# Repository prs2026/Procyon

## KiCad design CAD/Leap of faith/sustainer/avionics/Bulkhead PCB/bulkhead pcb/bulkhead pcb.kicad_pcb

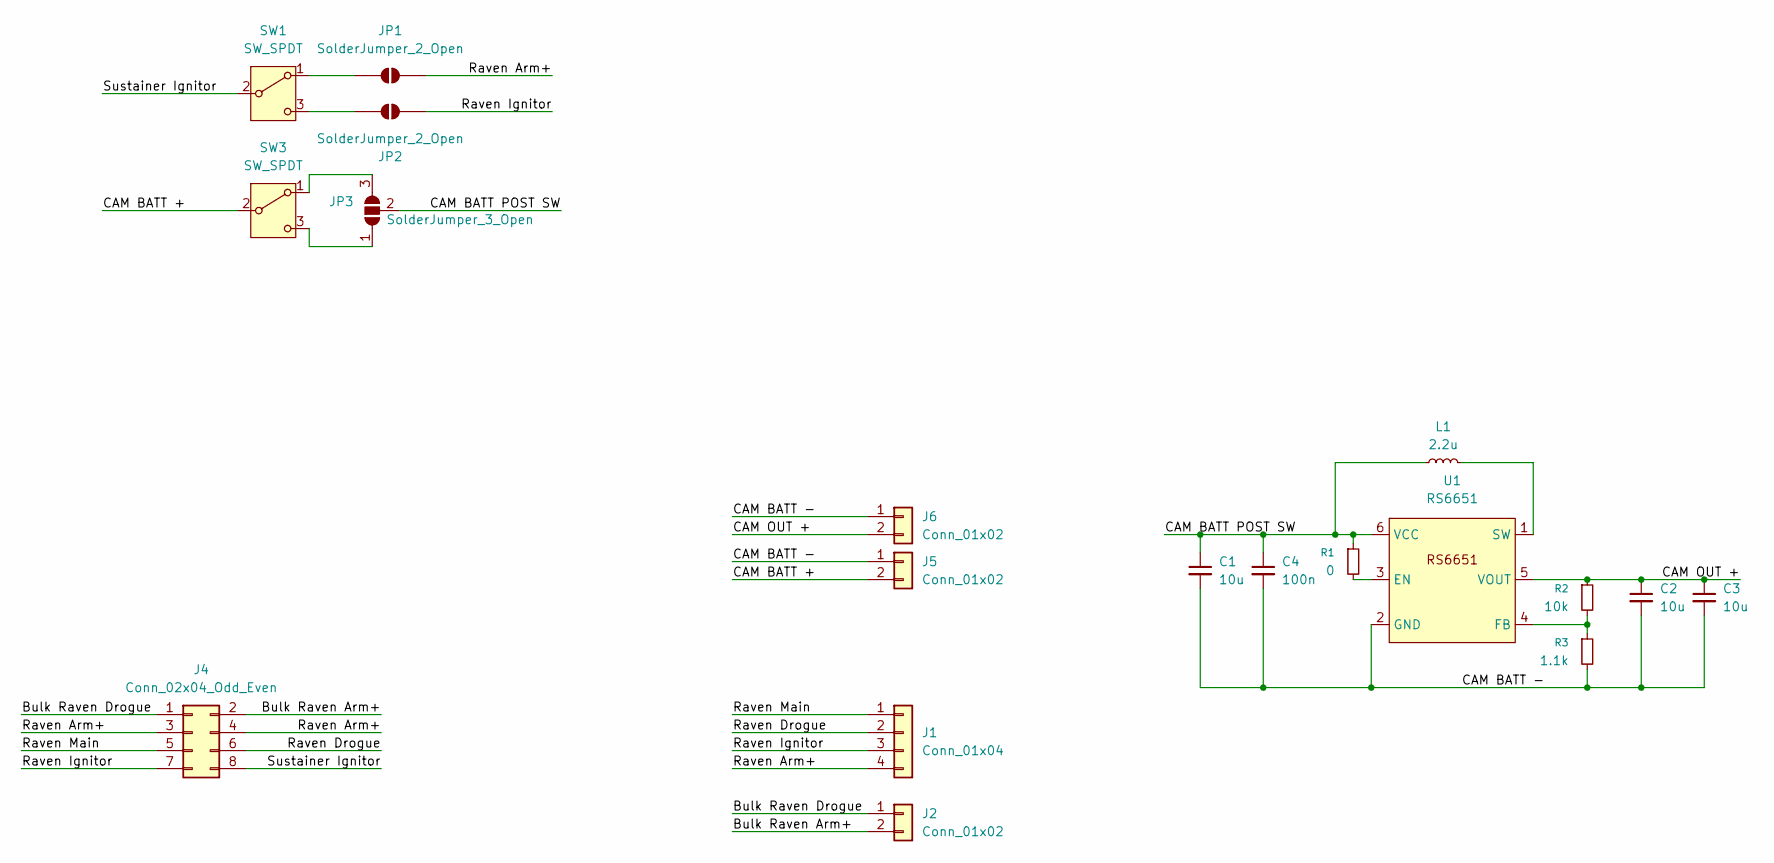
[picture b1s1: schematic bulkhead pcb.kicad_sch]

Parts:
C1, C2, C3: 10u; C_0603_1608Metric
C4: 100n; C_0603_1608Metric
J1: Conn_01x04; JST_PH_B4B-PH-K_1x04_P2.00mm_Vertical
J2, J5, J6: Conn_01x02; JST_PH_B2B-PH-K_1x02_P2.00mm_Vertical
J4: Conn_02x04_Odd_Even; PinHeader_2x04_P2.54mm_Vertical
JP1, JP2: SolderJumper_2_Open; SolderJumper-2_P1.3mm_Open_Pad1.0x1.5mm
JP3: SolderJumper_3_Open; SolderJumper-3_P1.3mm_Open_RoundedPad1.0x1.5mm
L1: 2.2u; L_Chilisin_BWVS00505020
R1: 0; R_0603_1608Metric
R2: 10k; R_0603_1608Metric
R3: 1.1k; R_0603_1608Metric
SW1, SW3: SW_SPDT; OMRON D2F-F-A1
U1: RS6651; SOT-23-6

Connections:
/Bulk Raven Arm+: J2.2, J4.2
/Bulk Raven Drogue: J2.1, J4.1
/CAM BATT +: J5.2, SW3.2 (B)
/CAM BATT -: C1.2, C2.2, C3.2, C4.2, J5.1, J6.1, R3.2, U1.2 (GND)
/CAM BATT POST SW: C1.1, C4.1, JP3.2 (C), L1.1, R1.1, U1.6 (VCC)
/CAM OUT +: C2.1, C3.1, J6.2, R2.1, U1.5 (VOUT)
/Raven Arm+: J1.4, J4.3, J4.4, JP1.1 (A)
/Raven Drogue: J1.2, J4.6
/Raven Ignitor: J1.3, J4.7, JP2.1 (A)
/Raven Main: J1.1, J4.5
/Sustainer Ignitor: J4.8, SW1.2 (B)
unnamed: JP1.2 (B), SW1.1 (A)
unnamed: JP2.2 (B), SW1.3 (C)
unnamed: JP3.1 (A), SW3.3 (C)
unnamed: JP3.3 (B), SW3.1 (A)
unnamed: R1.2, U1.3 (EN)
unnamed: R2.2, R3.1, U1.4 (FB)
unnamed: L1.2, U1.1 (SW)

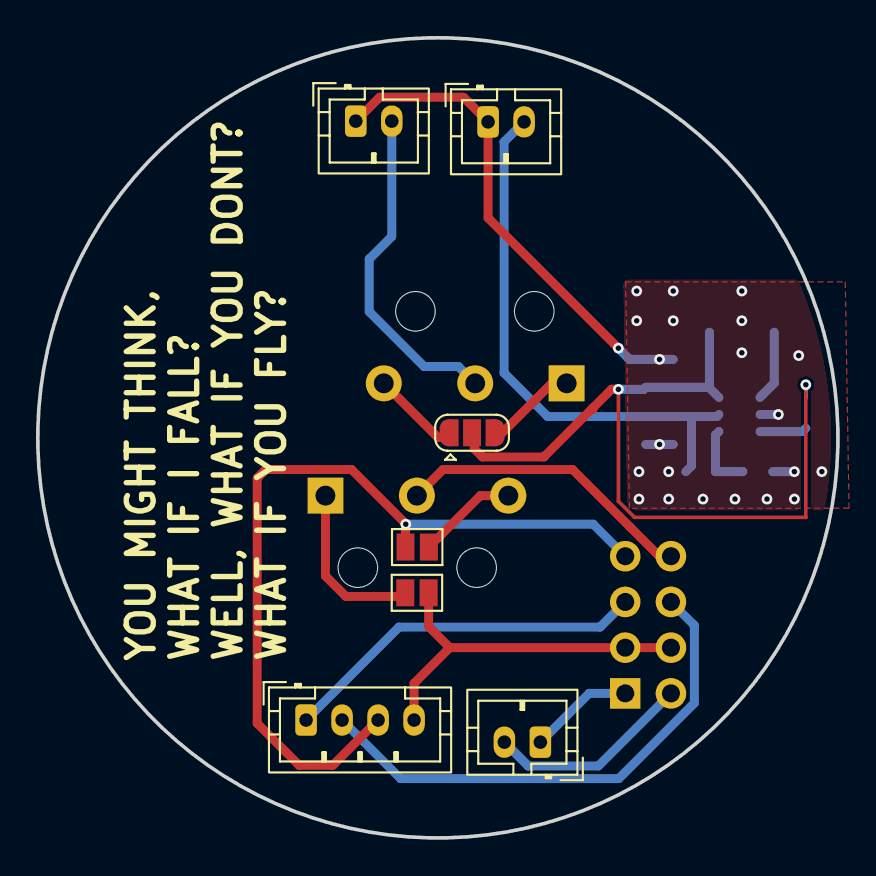
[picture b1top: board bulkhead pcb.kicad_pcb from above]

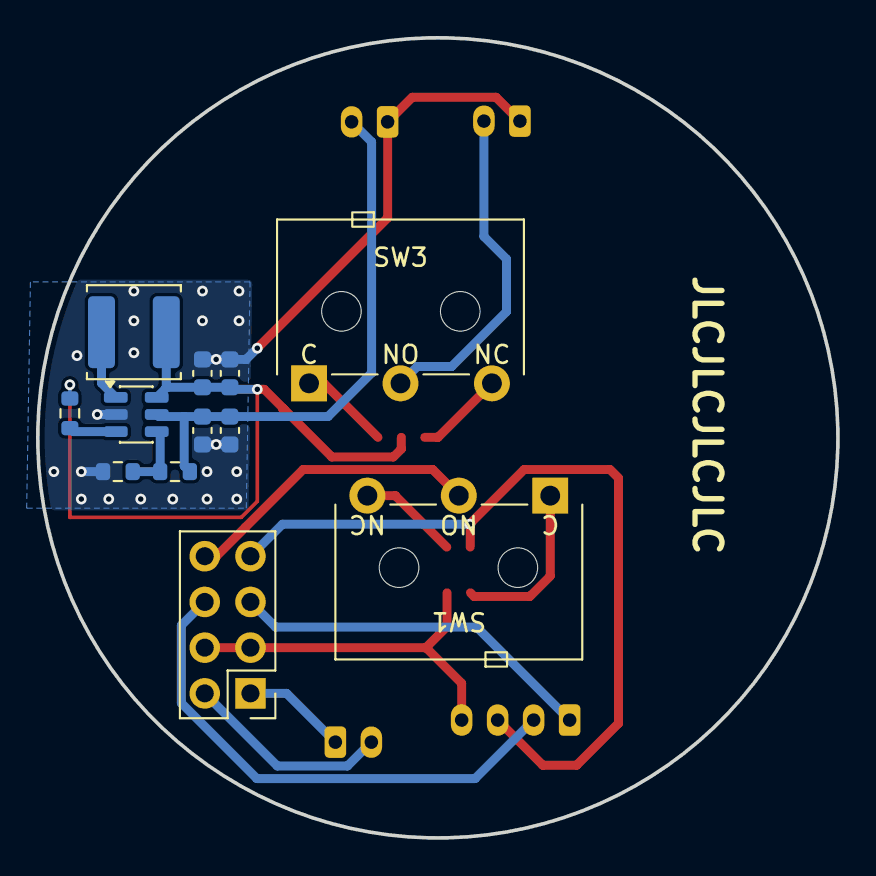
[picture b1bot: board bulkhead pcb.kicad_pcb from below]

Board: 2 copper layers, 44.5 x 44.4 mm, 19 parts (12 on the bottom side), 18 nets.

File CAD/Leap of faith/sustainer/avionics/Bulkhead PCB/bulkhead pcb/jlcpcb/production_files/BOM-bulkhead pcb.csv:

Comment,Designator,Footprint,LCSC,Quantity
Conn_01x02,J6,JST_PH_B2B-PH-K_1x02_P2.00mm_Vertical,,1
Conn_01x04,J1,JST_PH_B4B-PH-K_1x04_P2.00mm_Vertical,,1
Conn_01x02,J2,JST_PH_B2B-PH-K_1x02_P2.00mm_Vertical,,1
Conn_01x02,J5,JST_PH_B2B-PH-K_1x02_P2.00mm_Vertical,,1
Conn_02x04_Odd_Even,J4,PinHeader_2x04_P2.54mm_Vertical,,1
RS6651,U1,SOT-23-6,,1
10u,C2,C_0603_1608Metric,,1
2.2u,L1,L_Chilisin_BWVS00505020,,1
10k,R2,R_0603_1608Metric,,1
10u,C1,C_0603_1608Metric,,1
SW_SPDT,SW1,OMRON D2F-F-A1,,1
10u,C3,C_0603_1608Metric,,1
1k,R1,R_0603_1608Metric,,1
1.1k,R3,R_0603_1608Metric,,1
100n,C4,C_0603_1608Metric,,1
SW_SPDT,SW3,OMRON D2F-F-A1,,1

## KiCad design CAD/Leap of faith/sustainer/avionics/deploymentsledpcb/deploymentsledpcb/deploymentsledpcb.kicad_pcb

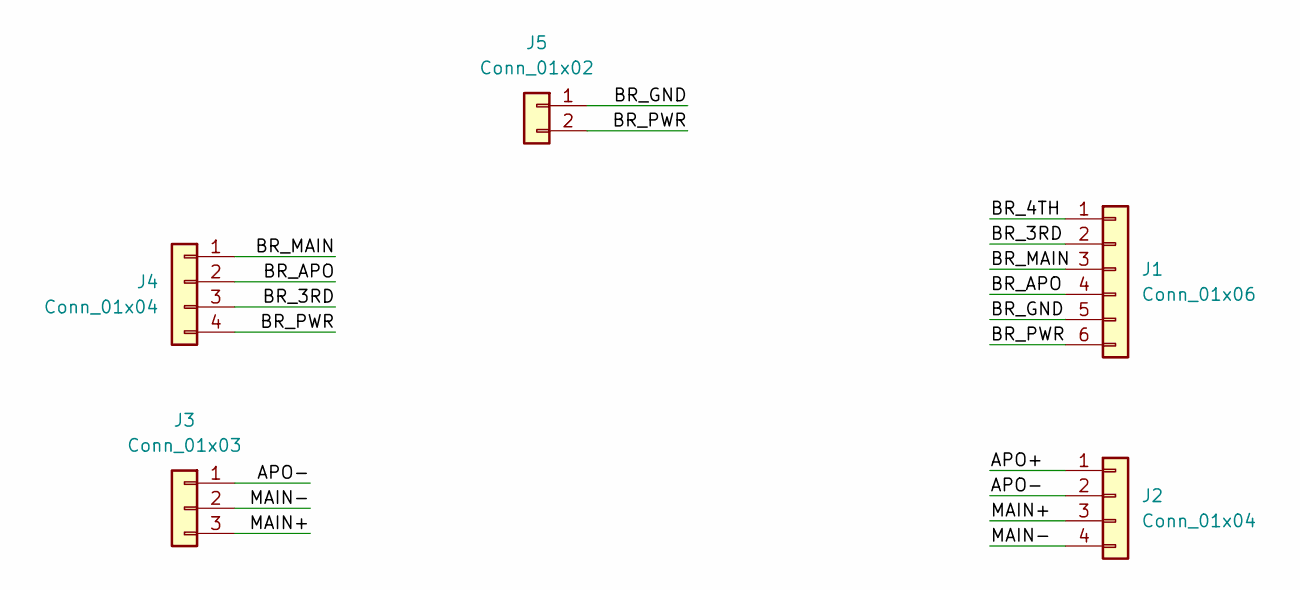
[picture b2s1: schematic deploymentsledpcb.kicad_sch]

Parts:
J1: Conn_01x06; PinHeader_1x06_P2.54mm_Vertical
J2, J4: Conn_01x04; JST_PH_B4B-PH-K_1x04_P2.00mm_Vertical
J3: Conn_01x03; JST_PH_B3B-PH-K_1x03_P2.00mm_Vertical
J5: Conn_01x02; JST_PH_B2B-PH-K_1x02_P2.00mm_Vertical

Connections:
/APO+: J2.1
/APO-: J2.2, J3.1
/BR_3RD: J1.2, J4.3
/BR_4TH: J1.1
/BR_APO: J1.4, J4.2
/BR_GND: J1.5, J5.1
/BR_MAIN: J1.3, J4.1
/BR_PWR: J1.6, J4.4, J5.2
/MAIN+: J2.3, J3.3
/MAIN-: J2.4, J3.2

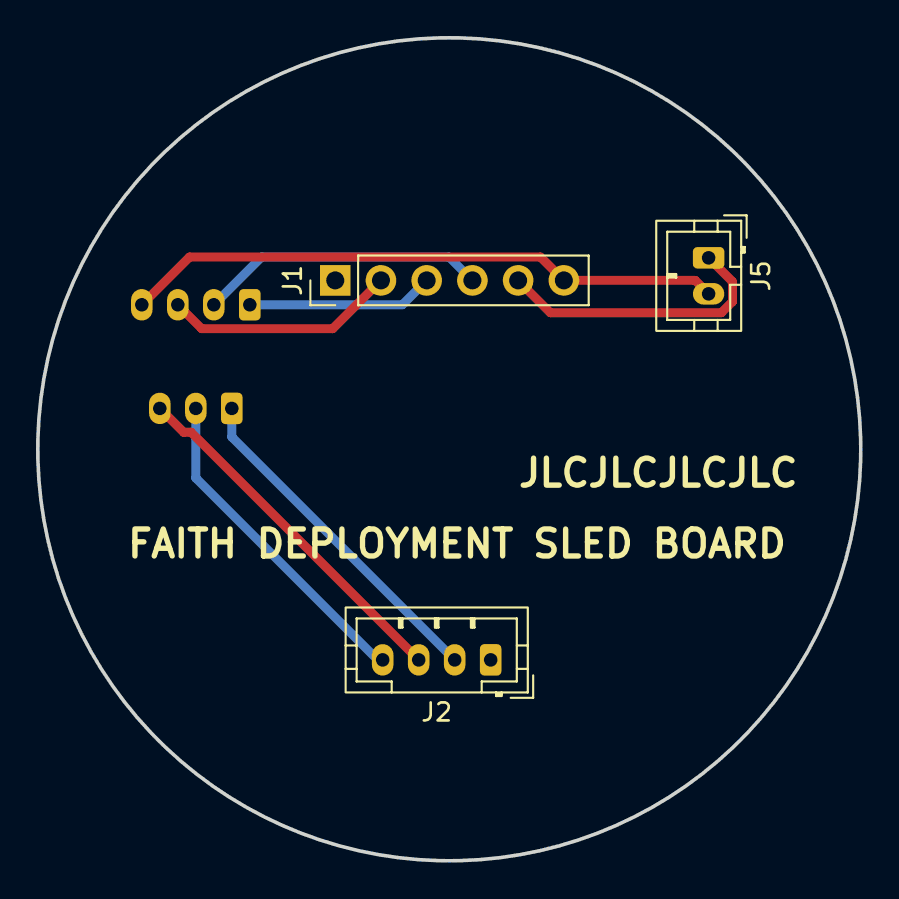
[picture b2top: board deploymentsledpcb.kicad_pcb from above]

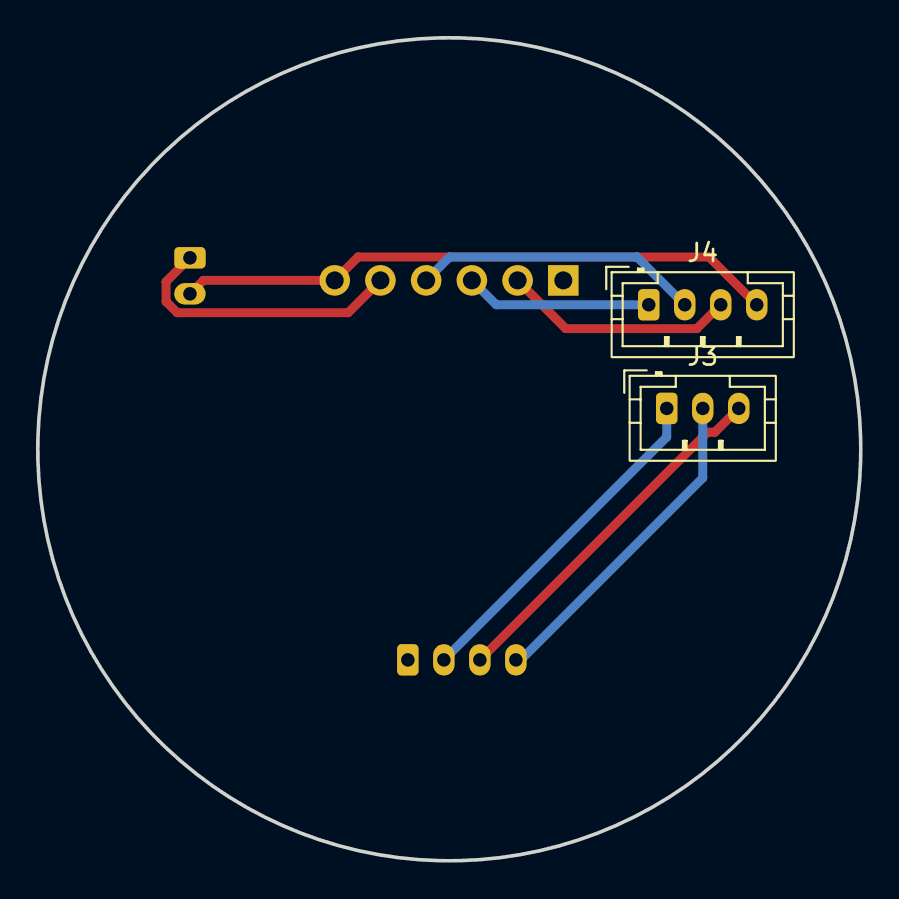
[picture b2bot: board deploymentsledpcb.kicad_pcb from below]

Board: 2 copper layers, 45.7 x 45.7 mm, 5 parts (2 on the bottom side), 8 nets.

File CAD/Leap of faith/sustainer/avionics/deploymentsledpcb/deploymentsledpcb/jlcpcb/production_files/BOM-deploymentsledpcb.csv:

Comment,Designator,Footprint,LCSC,Quantity
Conn_01x02,J5,JST_PH_B2B-PH-K_1x02_P2.00mm_Vertical,,1
Conn_01x04,J4,JST_PH_B4B-PH-K_1x04_P2.00mm_Vertical,,1
Conn_01x03,J3,JST_PH_B3B-PH-K_1x03_P2.00mm_Vertical,,1
Conn_01x04,J2,JST_PH_B4B-PH-K_1x04_P2.00mm_Vertical,,1
Conn_01x06,J1,PinHeader_1x06_P2.54mm_Vertical,,1

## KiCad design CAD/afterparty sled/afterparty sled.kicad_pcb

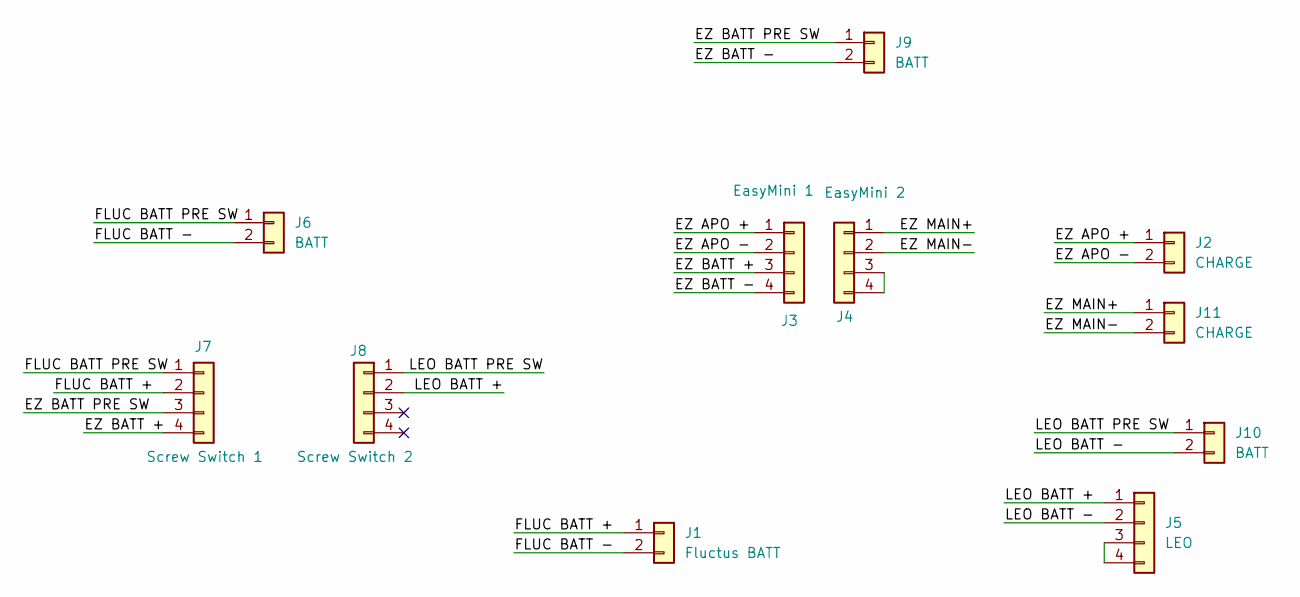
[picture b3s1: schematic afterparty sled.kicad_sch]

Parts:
J1: Fluctus BATT; PinHeader_1x02_P2.54mm_Vertical
J2, J11: CHARGE; PinHeader_1x02_P2.54mm_Vertical
J3: EasyMini 1; PinHeader_1x04_P2.54mm_Vertical
J4: EasyMini 2; PinHeader_1x04_P2.54mm_Vertical
J5: LEO; PinHeader_1x04_P2.54mm_Vertical
J6, J9, J10: BATT; PinHeader_1x02_P2.54mm_Vertical
J7: Screw Switch 1; PinHeader_1x04_P2.54mm_Vertical
J8: Screw Switch 2; PinHeader_1x04_P2.54mm_Vertical

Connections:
/EZ APO +: J2.1, J3.1
/EZ APO -: J2.2, J3.2
/EZ BATT +: J3.3, J7.4
/EZ BATT -: J3.4, J9.2
/EZ BATT PRE SW: J7.3, J9.1
/EZ MAIN+: J4.1, J11.1
/EZ MAIN-: J4.2, J11.2
/FLUC BATT +: J1.1, J7.2
/FLUC BATT -: J1.2, J6.2
/FLUC BATT PRE SW: J6.1, J7.1
/LEO BATT +: J5.1, J8.2
/LEO BATT -: J5.2, J10.2
/LEO BATT PRE SW: J8.1, J10.1
unnamed: J4.3, J4.4
unnamed: J5.3, J5.4

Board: 2 copper layers, 11 parts (0 on the bottom side), 15 nets, no tracks yet.

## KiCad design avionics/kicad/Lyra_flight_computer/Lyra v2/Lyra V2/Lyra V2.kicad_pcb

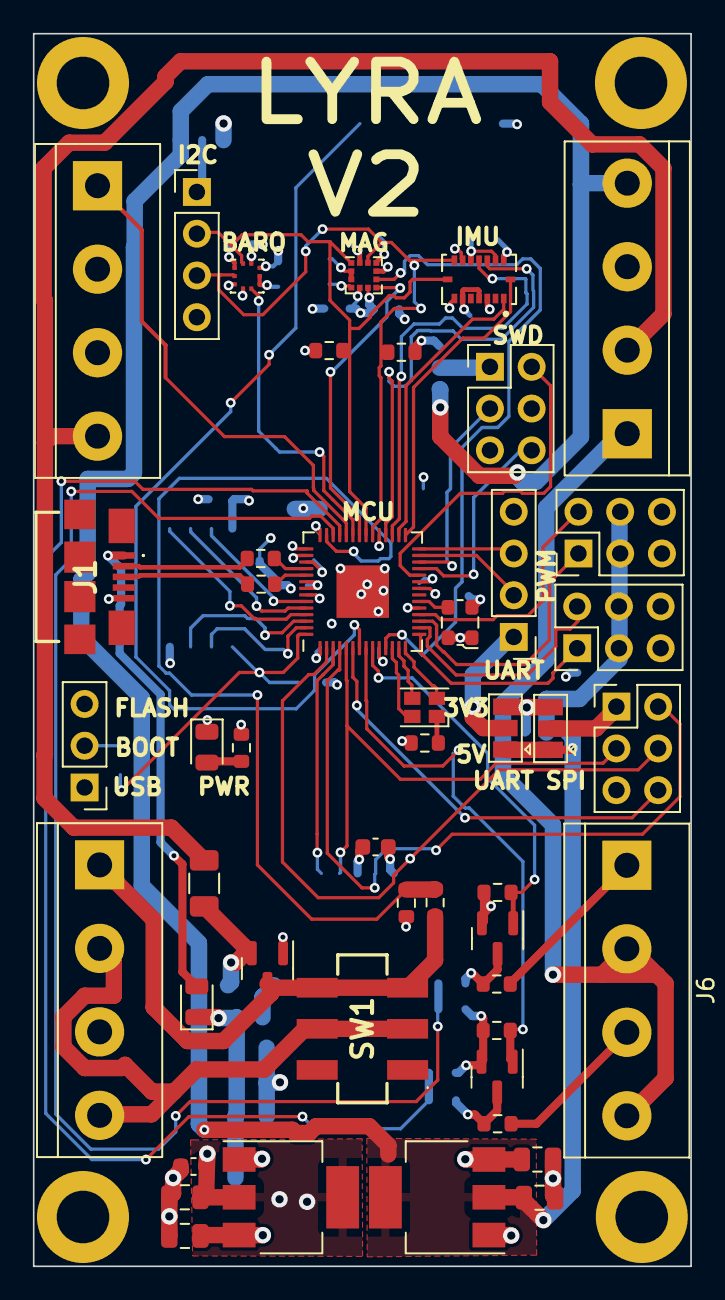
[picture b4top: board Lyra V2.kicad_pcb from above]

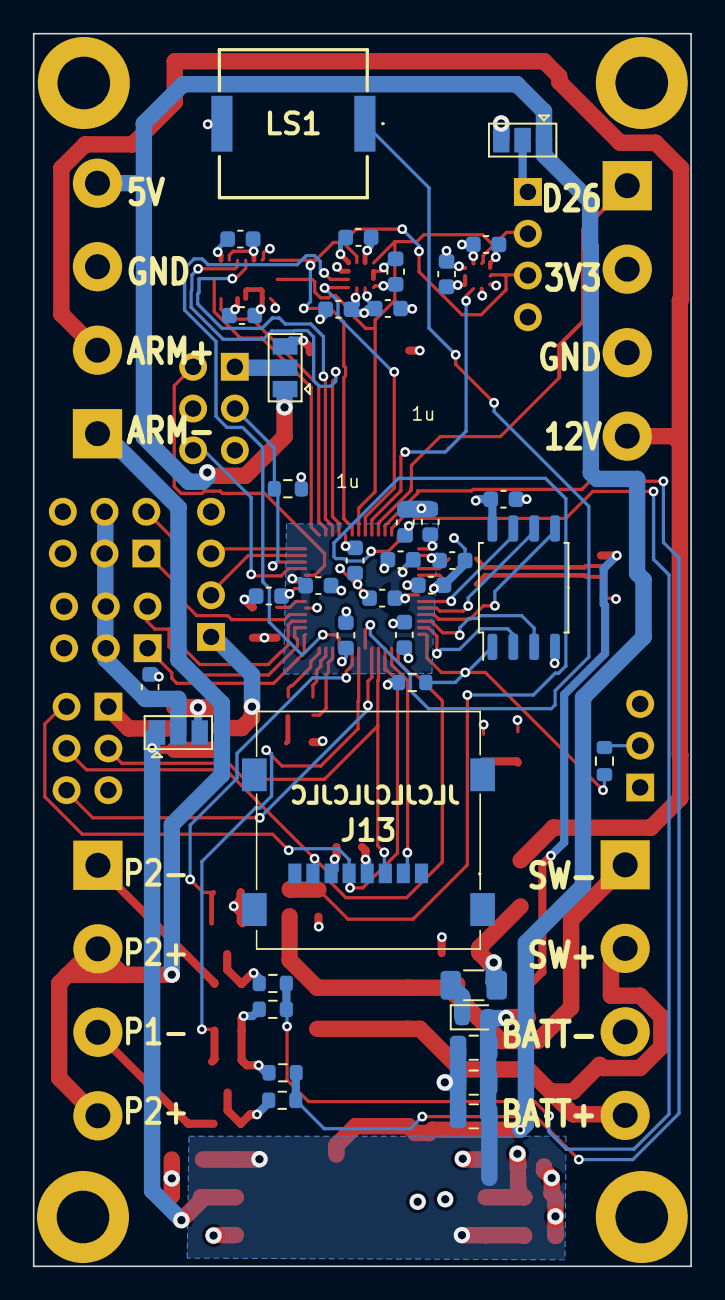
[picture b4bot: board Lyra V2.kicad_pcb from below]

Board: 4 copper layers, 40.0 x 75.0 mm, 90 parts (39 on the bottom side), 69 nets.

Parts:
C1, C4, C5, C6: 10u; C_0805_2012Metric
C2, C8: 22u; C_0805_2012Metric
C3, C9, C10, C14, C20, C21: 1u; C_0603_1608Metric
C7: 1u; C_0805_2012Metric
C11, C12, C13, C15, C16, C17, C18, C19, C22, C23, C24, C25, C27, C29, C30: 100n; C_0603_1608Metric
C26, C28: 100nf; C_0603_1608Metric
D1: D_Small; D_0805_2012Metric
D2: LED; LED_0805_2012Metric
D3: CLV1L-FKB; LED_Cree-PLCC4_2x2mm_CW
F1: 2a; Fuse_1206_3216Metric
F2: 200ma; Fuse_1206_3216Metric
FB1: FerriteBead_Small; D_0603_1608Metric
H1, H2, H3, H4: MountingHole_Pad; MountingHole_3.2mm_M3_DIN965_Pad
J1: USB_B_Micro; 101181920001LF
J2, J3, J5, J6: Screw_Terminal_01x04; TerminalBlock_bornier-4_P5.08mm
J4, J7, J8, J9: Conn_02x03_Odd_Even; PinHeader_2x03_P2.54mm_Vertical
J10, J11: Conn_01x04; PinHeader_1x04_P2.54mm_Vertical
J12: Conn_01x03; PinHeader_1x03_P2.54mm_Vertical
J13: MEM2067-02-180-00-A; MEM20670218000A
JP1, JP2, JP3, JP4, JP5: SolderJumper_3_Open; SolderJumper-3_P1.3mm_Open_Pad1.0x1.5mm
LS1: PKMCS0909E4000-R1; PKMCS0909E4000R1
Q1: AO3401A; SOT-23
Q2, Q3: BSS138; SOT-23
R1, R13: 1k; R_0603_1608Metric
R2, R3: 470R; R_0603_1608Metric
R4, R5: 10R; R_0603_1608Metric
R6, R8, R10: 20k; R_0603_1608Metric
R7, R9, R11: 6k; R_0603_1608Metric
R12: R_Small; R_0603_1608Metric
R14: DNF; R_0603_1608Metric
R15, R16: 27R; R_0603_1608Metric
R17, R18: 2k2; R_0603_1608Metric
R19: 10k; R_0603_1608Metric
SW1: SW_Push_DPDT; JS202011SCQN
U1: AZ1117-3.3; SOT-223-3_TabPin2
U2: AZ1117-5.0; SOT-223-3_TabPin2
U3: LIS3MDL; LGA-12_2x2mm_P0.5mm
U4: BMP390L; XDCR_BMP390L
U5: W25Q128JVS; SOIC-8_5.23x5.23mm_P1.27mm
U6: RP2040; QFN-56-1EP_7x7mm_P0.4mm_EP3.2x3.2mm
U7: BMI088; PQFN50P450X300X100-16N
X1: ECS-2520MV-xxx-xx; Oscillator_SMD_ECS_2520MV-xxx-xx-4Pin_2.5x2.0mm

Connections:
+1V1: C15.1, C17.1, C20.1, U6.23 (DVDD), U6.45 (VREG_VOUT), U6.50 (DVDD)
+3V3: C2.1, C3.1, C10.1, C11.1, C13.1, C14.2, C16.1, C18.1, C19.1, C21.1, C22.1, C23.1, C24.1, C25.1, C26.1, C27.1, C28.1, C29.1, C30.1, J2.2, J13.P4 (VDD), JP1.3 (B), JP2.3 (B), JP3.3 (B), JP4.3 (B), JP5.3 (B), R1.2, R12.2, R14.1, R17.1, R18.1, R19.1, U1.2 (VO), U3.5 (Vdd), U3.6 (Vdd_IO), U3.10 (~CS), U4.1 (VDDIO), U4.6 (~CS), U4.10 (VDD), U5.8 (VCC), U6.1 (IOVDD), U6.10 (IOVDD), U6.22 (IOVDD), U6.33 (IOVDD), U6.42 (IOVDD), U6.43 (ADC_AVDD), U6.44 (VREG_IN), U6.48 (USB_VDD), U6.49 (IOVDD), U7.3 (VDD), U7.7 (PS), U7.11 (VDDIO), U7.14 (CSB1), X1.1 (Tri-State), X1.4 (VDD)
+5V: C8.1, J5.4, JP1.1 (A), JP2.1 (A), JP3.1 (A), JP4.1 (A), JP5.1 (A), U2.2 (VO)
+12P: F1.2, J2.4, J5.2
+12V: J3.1, Q1.3 (D), R10.1, SW1.3 (C), SW1.4 (A)
+12VA: C1.1, C4.1, C5.1, C6.1, C7.1, D1.1 (K), FB1.2, U1.3 (VI), U2.3 (VI)
+BATT: J3.2, J3.4, SW1.2 (B), SW1.5 (B)
/ACCEL INT1: U6.29 (GPIO18), U7.16 (INT1)
/ACCEL INT2: U6.30 (GPIO19), U7.1 (INT2)
/BARO INT: U4.7 (INT/DNC), U6.37 (GPIO25)
/BATT SENSE: R10.2, R11.1, U6.41 (GPIO29_ADC3)
/BOOTSEL: J12.2, R13.2
/BRKOUT CS: J4.6, U6.6 (GPIO4)
/BUZZER: LS1.1 (+), U6.7 (GPIO5)
/GPIO26: J2.1, U6.38 (GPIO26_ADC0)
/GYRO INT3: U6.31 (GPIO20), U7.12 (INT3)
/GYRO INT4: U6.32 (GPIO21), U7.13 (INT4)
/I2C1 SCL: J10.2, R17.2, U3.1 (SCL/SPC), U4.2 (SCK/SCL), U6.35 (GPIO23), U7.8 (SCL/SCK)
/I2C1 SDA: J10.3, R18.2, U3.11 (SDA/SDI/SDO), U4.4 (SDI/SDO/SDA), U6.34 (GPIO22), U7.9 (SDA/SDI)
/I2C PWR: J10.1, JP2.2 (C)
/LEDBLUE: D3.4 (BK), U6.14 (GPIO11)
/LEDGREEN: D3.3 (GK), U6.13 (GPIO10)
/LEDRED: D3.2 (RK), U6.12 (GPIO9)
/MAG DRDY: U3.8 (DRDY), U6.11 (GPIO8)
/MAG INT: U3.7 (INT), U6.36 (GPIO24)
/P1 CONT: R6.2, R7.1, U6.40 (GPIO28_ADC2)
/P1 EN: Q3.1 (G), R3.2, U6.8 (GPIO6)
/P1-: J6.3, R5.1
/P2 CONT: R8.2, R9.1, U6.39 (GPIO27_ADC1)
/P2 EN: Q2.1 (G), R2.2, U6.9 (GPIO7)
/P2-: J6.1, R4.1
/PYRO PWR: J5.1, J6.2, J6.4
/QSPI_SCLK: U5.6 (CLK), U6.52 (QSPI_SCLK)
/QSPI_SD1: U5.2 (DO(IO1)), U6.55 (QSPI_SD1)
/QSPI_SD2: U5.3 (IO2), U6.54 (QSPI_SD2)
/QSPI_SD3: U5.7 (IO3), U6.51 (QSPI_SD3)
/QSPI_SDO: U5.5 (DI(IO0)), U6.53 (QSPI_SD0)
/QSPI_SS: R13.1, R14.2, U5.1 (~CS), U6.56 (QSPI_SS)
/RP USB_D+: R15.2, U6.47 (USB_DP)
/RP USB_D-: R16.1, U6.46 (USB_DM)
/RUN: J7.3, R19.2, U6.26 (RUN)
/SD CS: J13.P2 (CD/DAT3), U6.3 (GPIO1)
/SERVO1: J9.1, U6.15 (GPIO12)
/SERVO2: J9.2, U6.16 (GPIO13)
/SERVO3: J8.1, U6.17 (GPIO14)
/SERVO4: J8.2, U6.18 (GPIO15)
/SERVO PWR: C9.1, J8.3, J8.4, J9.3, J9.4, JP1.2 (C)
/SPI0 MISO: J4.4, J13.P7 (DAT0), U6.2 (GPIO0)
/SPI0 MOSI: J4.3, J13.P3 (CMD), U6.5 (GPIO3)
/SPI0 SCLK: J4.2, J13.P5 (CLK), U6.4 (GPIO2)
/SPI PWR: J4.1, JP3.2 (C)
/SWCLK: J7.2, U6.24 (SWCLK)
/SWD: J7.6, U6.25 (SWD)
/SWD PWR: J7.1, JP5.2 (C)
/UART0 RX: J11.3, U6.28 (GPIO17)
/UART0 TX: J11.2, U6.27 (GPIO16)
/UART PWR: J11.1, JP4.2 (C)
/USB_D+: J1.3 (D+), R15.1
/USB_D-: J1.2 (D-), R16.2
/XIN: U6.20 (XIN), X1.3 (OUT)
GND: C1.2, C2.2, C3.2, C4.2, C5.2, C6.2, C7.2, C8.2, C9.2, C10.2, C11.2, C12.2, C13.2, C14.1, C15.2, C16.2, C17.2, C18.2, C19.2, C20.2, C21.2, C22.2, C23.2, C24.2, C25.2, C26.2, C27.2, C28.2, C29.2, C30.2, D2.1 (K), H1.1, H2.1, H3.1, H4.1, J1.5 (GND), J2.3, J3.3, J4.5, J5.3, J7.4, J7.5, J8.5, J8.6, J9.5, J9.6, J10.4, J11.4, J12.1, J13.P6 (VSS), LS1.2 (-), Q1.1 (G), Q2.2 (S), Q3.2 (S), R2.1, R3.1, R7.2, R9.2, R11.2, U1.1 (GND), U2.1 (GND), U3.2 (GND), U3.3 (GND), U3.9 (SDO/SA1), U3.12 (GND), U4.3 (VSS/GND), U4.5 (SDO/DNC/SA0), U4.8 (VSS/GND__1), U4.9 (VSS/GND__2), U5.4 (GND), U6.19 (TESTEN), U6.57 (GND), U7.4 (GNDA), U7.6 (GNDIO), U7.10 (SDO2), U7.15 (SDO1), X1.2 (GND)
unnamed: D2.2 (A), R1.1
unnamed: D3.1 (A), R12.1
unnamed: F2.2, FB1.1
unnamed: F1.1, F2.1, Q1.2 (S)
unnamed: Q2.3 (D), R4.2, R6.1
unnamed: Q3.3 (D), R5.2, R8.1
unnamed: C12.1, U3.4 (C1)
VBUS: D1.2 (A), J1.1 (VBUS)

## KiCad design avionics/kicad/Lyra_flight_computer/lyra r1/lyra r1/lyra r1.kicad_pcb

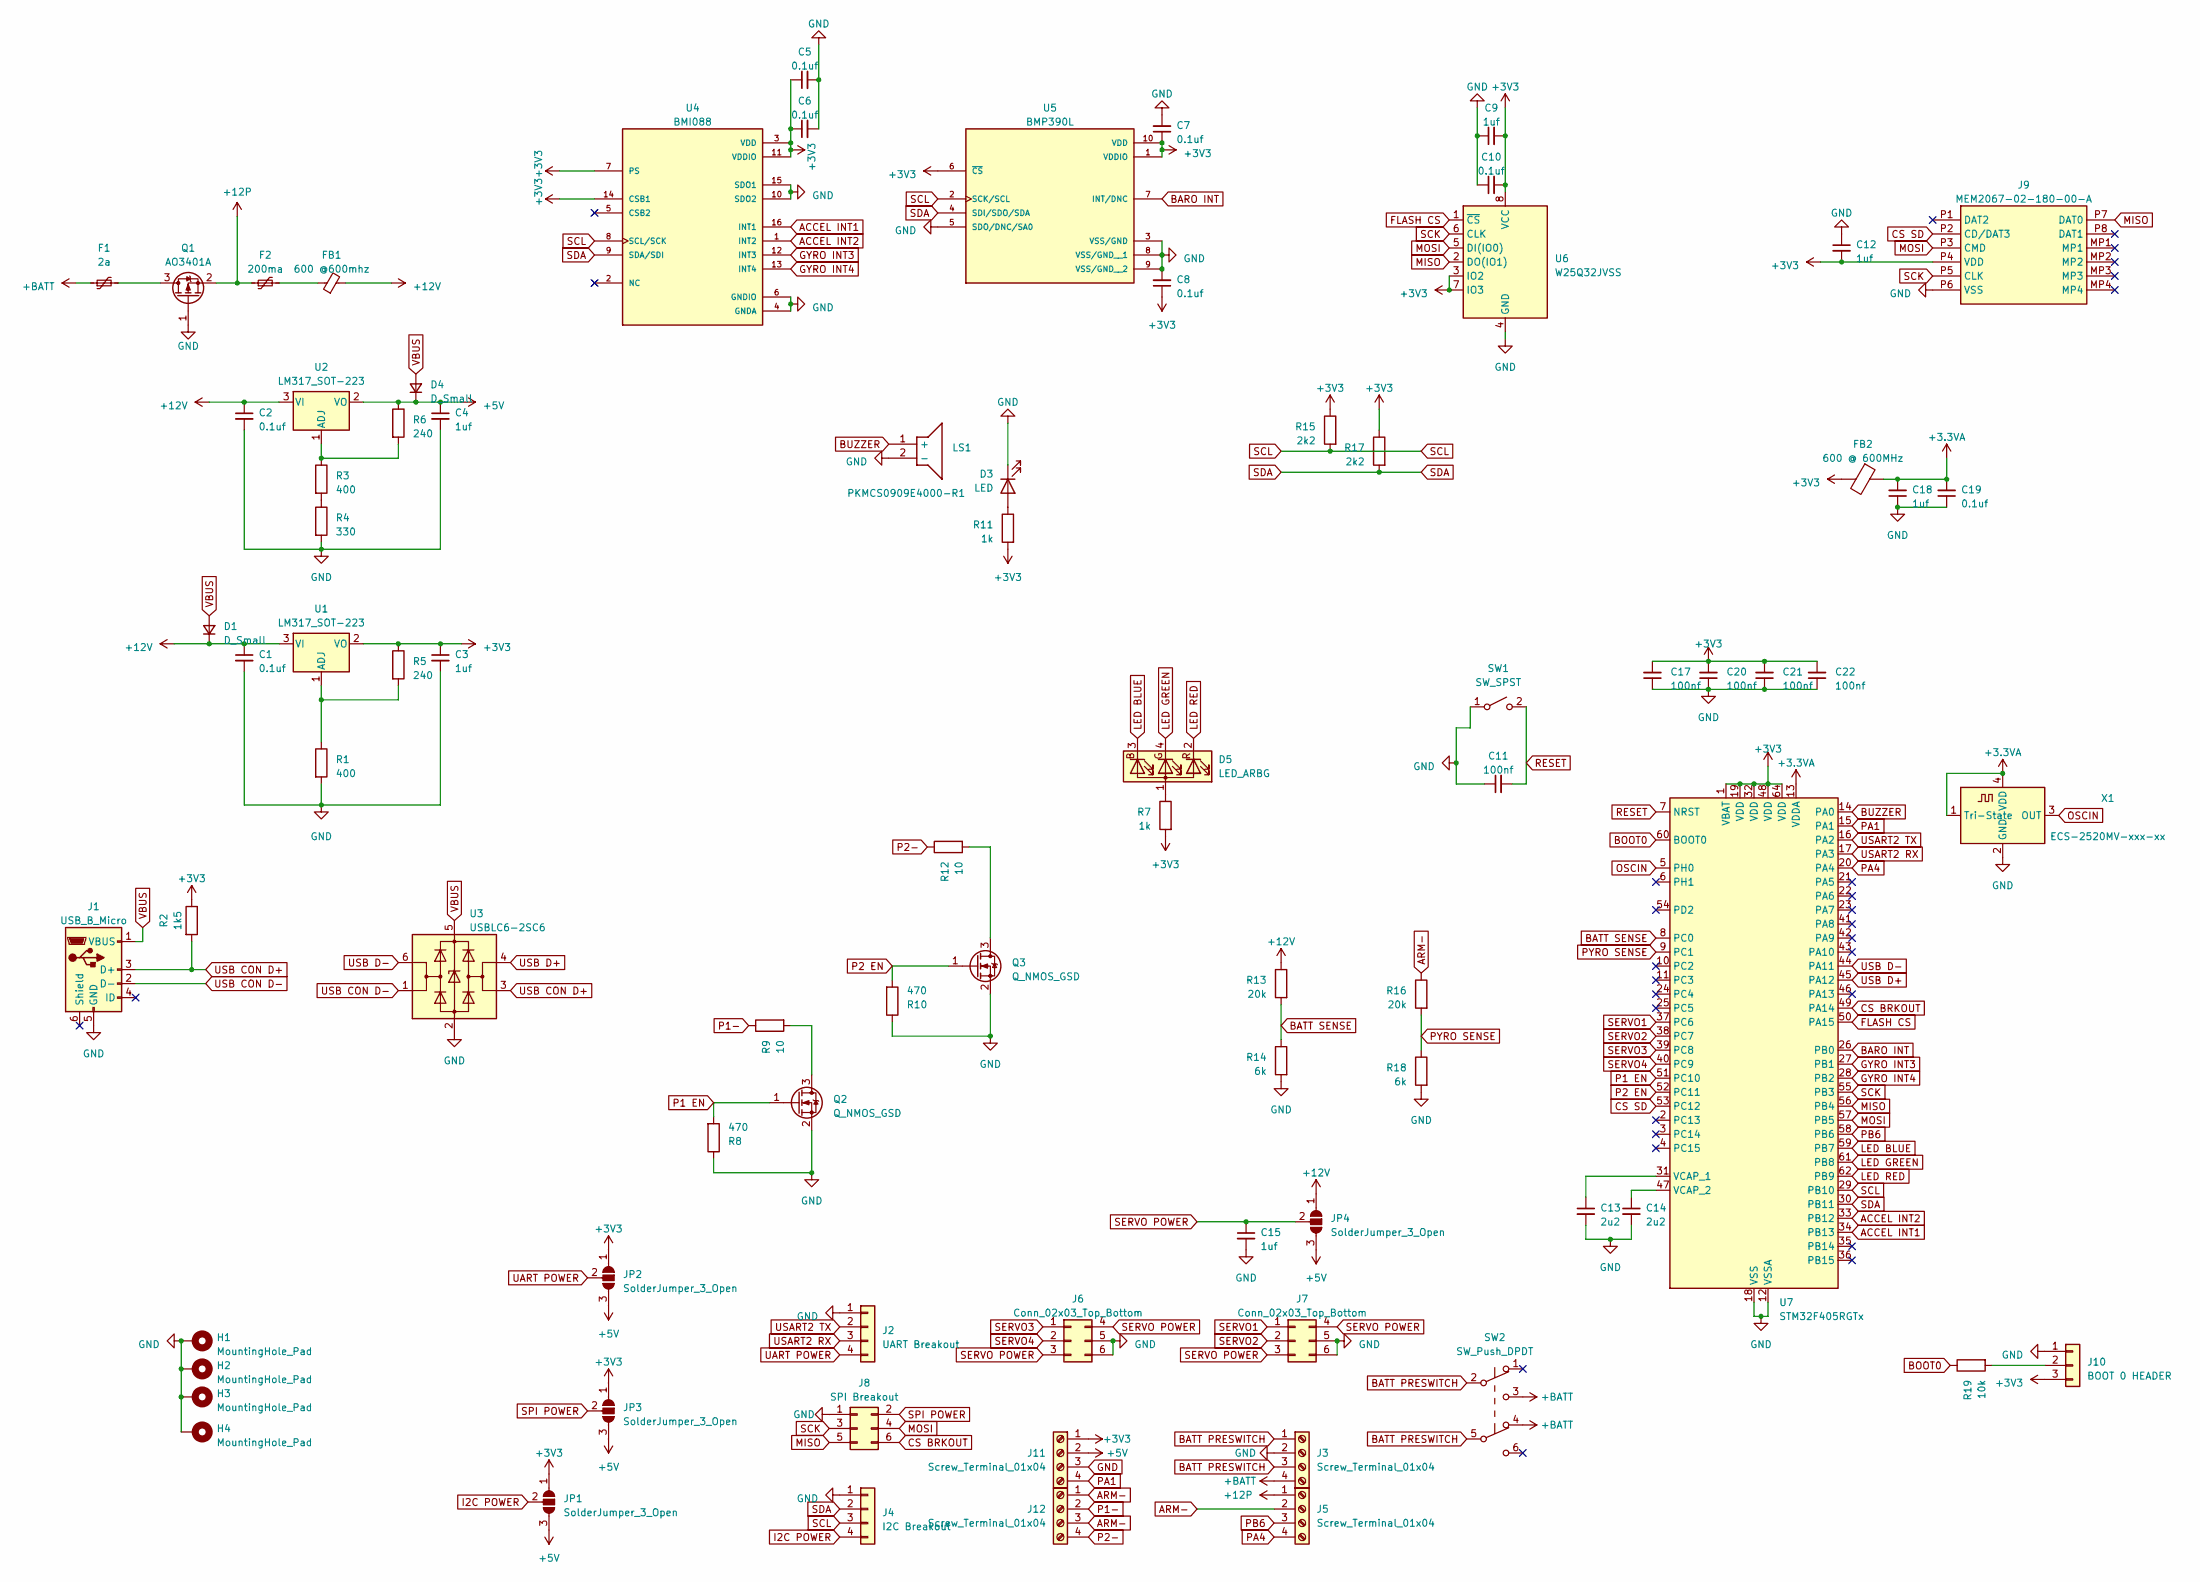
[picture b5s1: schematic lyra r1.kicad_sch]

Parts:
C1, C2: 0.1uf; C_0805_2012Metric
C3, C4, C15: 1uf; C_0805_2012Metric
C5, C6, C7, C8, C10, C19: 0.1uf; C_0603_1608Metric
C9, C12, C18: 1uf; C_0603_1608Metric
C11, C17, C20, C21, C22: 100nf; C_0603_1608Metric
C13, C14: 2u2; C_0603_1608Metric
D1, D4: D_Small; D_0805_2012Metric
D3: LED; LED_0805_2012Metric
D5: LED_ARBG; LED_Cree-PLCC4_2x2mm_CW
F1: 2a; Fuse_1206_3216Metric
F2: 200ma; Fuse_1206_3216Metric
FB1: 600 @600mhz; L_0603_1608Metric
FB2: 600 @ 600MHz; L_0603_1608Metric
H1, H2, H3, H4: MountingHole_Pad; MountingHole_3.2mm_M3_DIN965_Pad
J1: USB_B_Micro; USB_Micro-B_Amphenol_10104110_Horizontal
J2: UART Breakout; PinHeader_1x04_P2.54mm_Vertical
J3, J5, J11, J12: Screw_Terminal_01x04; TerminalBlock_bornier-4_P5.08mm
J4: I2C Breakout; PinHeader_1x04_P2.54mm_Vertical
J6, J7: Conn_02x03_Top_Bottom; PinHeader_2x03_P2.54mm_Vertical
J8: SPI Breakout; PinHeader_2x03_P2.54mm_Vertical
J9: MEM2067-02-180-00-A; MEM20670218000A; Mouser Part Number 640-MEM20670218000A
J10: BOOT 0 HEADER; PinHeader_1x03_P2.54mm_Vertical
JP1, JP2, JP3, JP4: SolderJumper_3_Open; SolderJumper-3_P1.3mm_Open_Pad1.0x1.5mm
LS1: PKMCS0909E4000-R1; PKMCS0909E4000R1; Mouser Part Number 81-PKMCS0909E4000-R1
Q1: AO3401A; SOT-23-3
Q2, Q3: Q_NMOS_GSD; SOT-23-3
R1: 400; R_0603_1608Metric
R2: 1k5; R_0603_1608Metric
R3: 400; R_0603_1608Metric_Pad0.98x0.95mm_HandSolder
R4: 330; R_0603_1608Metric_Pad0.98x0.95mm_HandSolder
R5, R6: 240; R_0603_1608Metric_Pad0.98x0.95mm_HandSolder
R7, R11: 1k; R_0603_1608Metric
R8, R10: 470; R_0603_1608Metric
R9, R12: 10; R_0603_1608Metric
R13, R16: 20k; R_0603_1608Metric
R14, R18: 6k; R_0603_1608Metric
R15, R17: 2k2; R_0603_1608Metric
R19: 10k; R_0603_1608Metric
SW1: SW_SPST; SW_SPST_CK_RS282G05A3
SW2: SW_Push_DPDT; JS202011SCQN
U1, U2: LM317_SOT-223; SOT-223-3_TabPin2
U3: USBLC6-2SC6; SOT-23-6
U4: BMI088; PQFN50P450X300X100-16N
U5: BMP390L; XDCR_BMP390L; PARTREV 1.7
U6: W25Q32JVSS; SOIC-8_5.23x5.23mm_P1.27mm
U7: STM32F405RGTx; LQFP-64_10x10mm_P0.5mm
X1: ECS-2520MV-xxx-xx; Oscillator_SMD_ECS_2520MV-xxx-xx-4Pin_2.5x2.0mm

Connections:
+3.3VA: C18.2, C19.2, FB2.1, U7.13 (VDDA), X1.1 (Tri-State), X1.4 (VDD)
+3V3: C3.1, C5.1, C6.1, C7.1, C8.1, C9.2, C10.2, C12.2, C17.2, C20.2, C21.2, C22.2, FB2.2, J9.P4 (VDD), J10.3, J11.1, JP1.1 (A), JP2.1 (A), JP3.1 (A), R2.1, R5.1, R7.2, R11.2, R15.1, R17.1, U1.2 (VO), U4.3 (VDD), U4.7 (PS), U4.11 (VDDIO), U4.14 (CSB1), U5.1 (VDDIO), U5.6 (~CS), U5.10 (VDD), U6.3 (IO2), U6.7 (IO3), U6.8 (VCC), U7.1 (VBAT), U7.19 (VDD), U7.32 (VDD), U7.48 (VDD), U7.64 (VDD)
+5V: C4.1, D4.1 (K), J11.2, JP1.3 (B), JP2.3 (B), JP3.3 (B), JP4.3 (B), R6.1, U2.2 (VO)
+12P: F2.1, J5.1, Q1.2 (S)
+12V: C1.1, C2.1, D1.1 (K), FB1.2, JP4.1 (A), R13.1, U1.3 (VI), U2.3 (VI)
+BATT: F1.1, J3.4, SW2.3 (C), SW2.4 (A)
ACCEL INT1: U4.16 (INT1), U7.34 (PB13)
ACCEL INT2: U4.1 (INT2), U7.33 (PB12)
ARM-: J5.2, J12.1, J12.3, R16.1
BARO INT: U5.7 (INT/DNC), U7.26 (PB0)
BATT PRESWITCH: J3.1, J3.3, SW2.2 (B), SW2.5 (B)
BATT SENSE: R13.2, R14.1, U7.8 (PC0)
BOOT0: R19.1, U7.60 (BOOT0)
BUZZER: LS1.1 (+), U7.14 (PA0)
CS BRKOUT: J8.6, U7.49 (PA14)
CS SD: J9.P2 (CD/DAT3), U7.53 (PC12)
FLASH CS: U6.1 (~CS), U7.50 (PA15)
GND: C1.2, C2.2, C3.2, C4.2, C5.2, C6.2, C7.2, C8.2, C9.1, C10.1, C11.1, C12.1, C13.2, C14.2, C15.2, C17.1, C18.1, C19.1, C20.1, C21.1, C22.1, D3.1 (K), H1.1, H2.1, H3.1, H4.1, J1.5 (GND), J2.1, J3.2, J4.1, J6.5, J6.6, J7.5, J7.6, J8.1, J9.P6 (VSS), J10.1, J11.3, LS1.2 (-), Q1.1 (G), Q2.2 (S), Q3.2 (S), R1.2, R4.2, R8.1, R10.1, R14.2, R18.2, SW1.1 (A), U3.2 (GND), U4.4 (GNDA), U4.6 (GNDIO), U4.10 (SDO2), U4.15 (SDO1), U5.3 (VSS/GND), U5.5 (SDO/DNC/SA0), U5.8 (VSS/GND__1), U5.9 (VSS/GND__2), U6.4 (GND), U7.12 (VSSA), U7.18 (VSS), U7.63 (VSS), X1.2 (GND)
GYRO INT3: U4.12 (INT3), U7.27 (PB1)
GYRO INT4: U4.13 (INT4), U7.28 (PB2)
I2C POWER: J4.4, JP1.2 (C)
LED BLUE: D5.3 (BK), U7.59 (PB7)
LED GREEN: D5.4 (GK), U7.61 (PB8)
LED RED: D5.2 (RK), U7.62 (PB9)
MISO: J8.5, J9.P7 (DAT0), U6.2 (DO(IO1)), U7.56 (PB4)
MOSI: J8.4, J9.P3 (CMD), U6.5 (DI(IO0)), U7.57 (PB5)
unnamed: D3.2 (A), R11.1
unnamed: D5.1 (A), R7.1
unnamed: F2.2, FB1.1
unnamed: J10.2, R19.2
unnamed: F1.2, Q1.3 (D)
unnamed: Q2.3 (D), R9.2
unnamed: Q3.3 (D), R12.2
unnamed: R3.2, R4.1
unnamed: R1.1, R5.2, U1.1 (ADJ)
unnamed: R3.1, R6.2, U2.1 (ADJ)
unnamed: C13.1, U7.31 (VCAP_1)
unnamed: C14.1, U7.47 (VCAP_2)
OSCIN: U7.5 (PH0), X1.3 (OUT)
P1 EN: Q2.1 (G), R8.2, U7.51 (PC10)
P1-: J12.2, R9.1
P2 EN: Q3.1 (G), R10.2, U7.52 (PC11)
P2-: J12.4, R12.1
PA1: J11.4, U7.15 (PA1)
PA4: J5.4, U7.20 (PA4)
PB6: J5.3, U7.58 (PB6)
PYRO SENSE: R16.2, R18.1, U7.9 (PC1)
RESET: C11.2, SW1.2 (B), U7.7 (NRST)
SCK: J8.3, J9.P5 (CLK), U6.6 (CLK), U7.55 (PB3)
SCL: J4.3, R15.2, U4.8 (SCL/SCK), U5.2 (SCK/SCL), U7.29 (PB10)
SDA: J4.2, R17.2, U4.9 (SDA/SDI), U5.4 (SDI/SDO/SDA), U7.30 (PB11)
SERVO1: J7.1, U7.37 (PC6)
SERVO2: J7.2, U7.38 (PC7)
SERVO3: J6.1, U7.39 (PC8)
SERVO4: J6.2, U7.40 (PC9)
SERVO POWER: C15.1, J6.3, J6.4, J7.3, J7.4, JP4.2 (C)
SPI POWER: J8.2, JP3.2 (C)
UART POWER: J2.4, JP2.2 (C)
USART2 RX: J2.3, U7.17 (PA3)
USART2 TX: J2.2, U7.16 (PA2)
USB CON D+: J1.3 (D+), R2.2, U3.3 (I/O2)
USB CON D-: J1.2 (D-), U3.1 (I/O1)
USB D+: U3.4 (I/O2), U7.45 (PA12)
USB D-: U3.6 (I/O1), U7.44 (PA11)
VBUS: D1.2 (A), D4.2 (A), J1.1 (VBUS), U3.5 (VBUS)

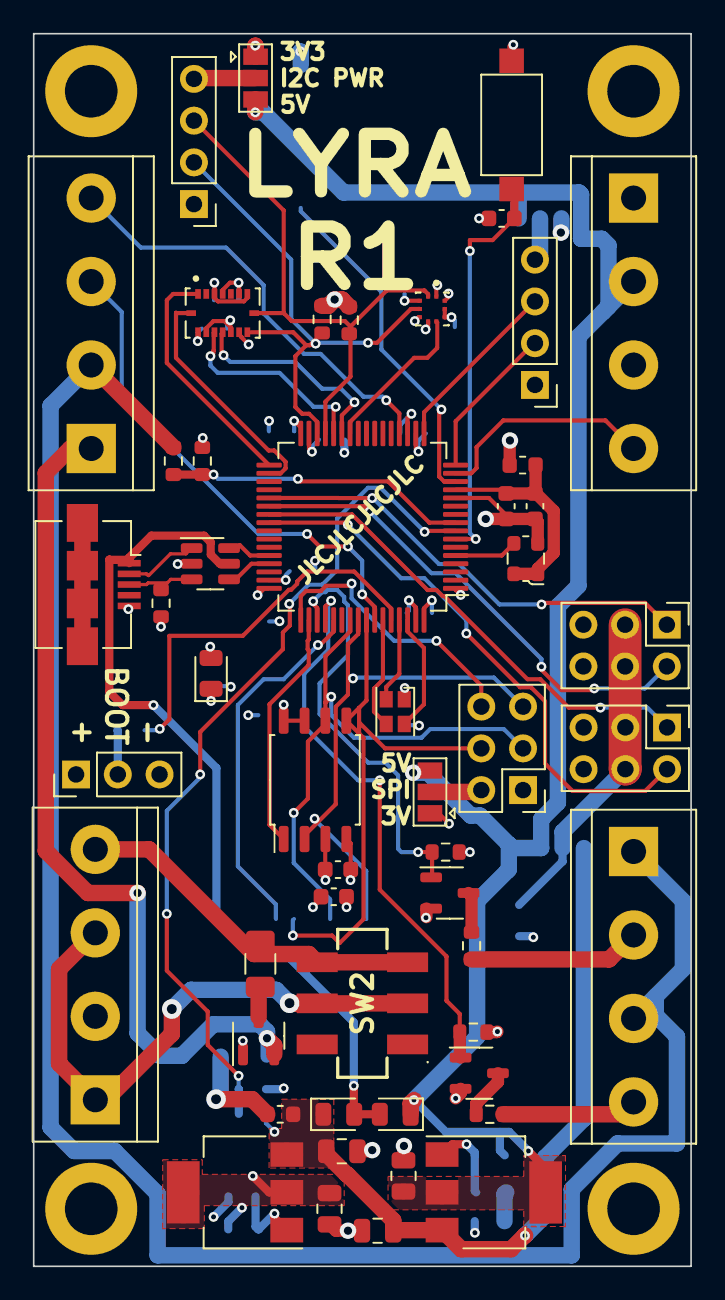
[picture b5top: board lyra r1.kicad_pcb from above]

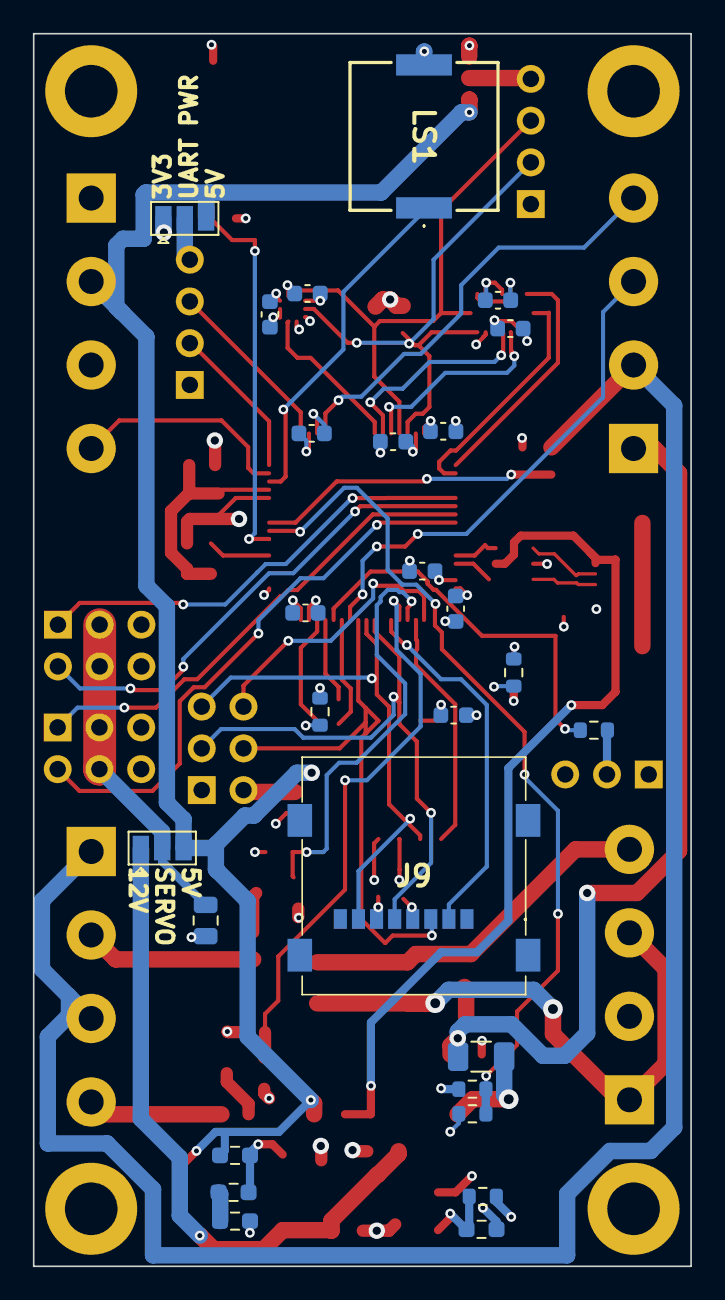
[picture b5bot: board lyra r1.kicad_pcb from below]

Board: 4 copper layers, 40.0 x 75.0 mm, 82 parts (27 on the bottom side), 65 nets.
